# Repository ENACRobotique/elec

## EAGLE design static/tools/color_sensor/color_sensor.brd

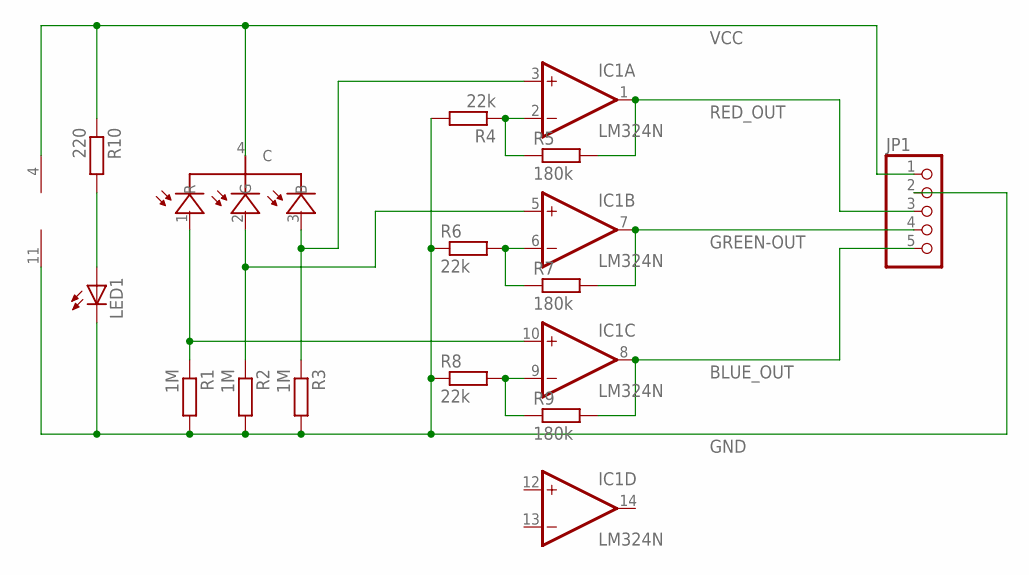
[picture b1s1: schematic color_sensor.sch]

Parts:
IC1: LM324N; DIL14
JP1: PINHD-1X5; 1X05
LED1: LED5MM
R1, R2, R3: 1M; 0207/10
R4, R6, R8: 22k; 0207/10
R5, R7, R9: 180k; 0207/10
R10: 220; 0207/10
U$1: KPS-5130PD7C

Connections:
BLUE_OUT: IC1.8 (OUT), JP1.5, R9.2
GND: IC1.11 (V-), JP1.2, LED1.K (C), R1.2, R2.2, R3.2, R4.2, R6.1, R8.1
GREEN-OUT: IC1.7 (OUT), JP1.4, R7.2
unnamed: IC1.10 (+IN), R1.1, U$1.1 (R)
unnamed: IC1.5 (+IN), R2.1, U$1.2 (G)
unnamed: IC1.3 (+IN), R3.1, U$1.3 (B)
unnamed: LED1.A, R10.2
unnamed: IC1.2 (-IN), R4.1, R5.1
unnamed: IC1.6 (-IN), R6.2, R7.1
unnamed: IC1.9 (-IN), R8.2, R9.1
RED_OUT: IC1.1 (OUT), JP1.3, R5.2
VCC: IC1.4 (V+), JP1.1, R10.1, U$1.4 (C)

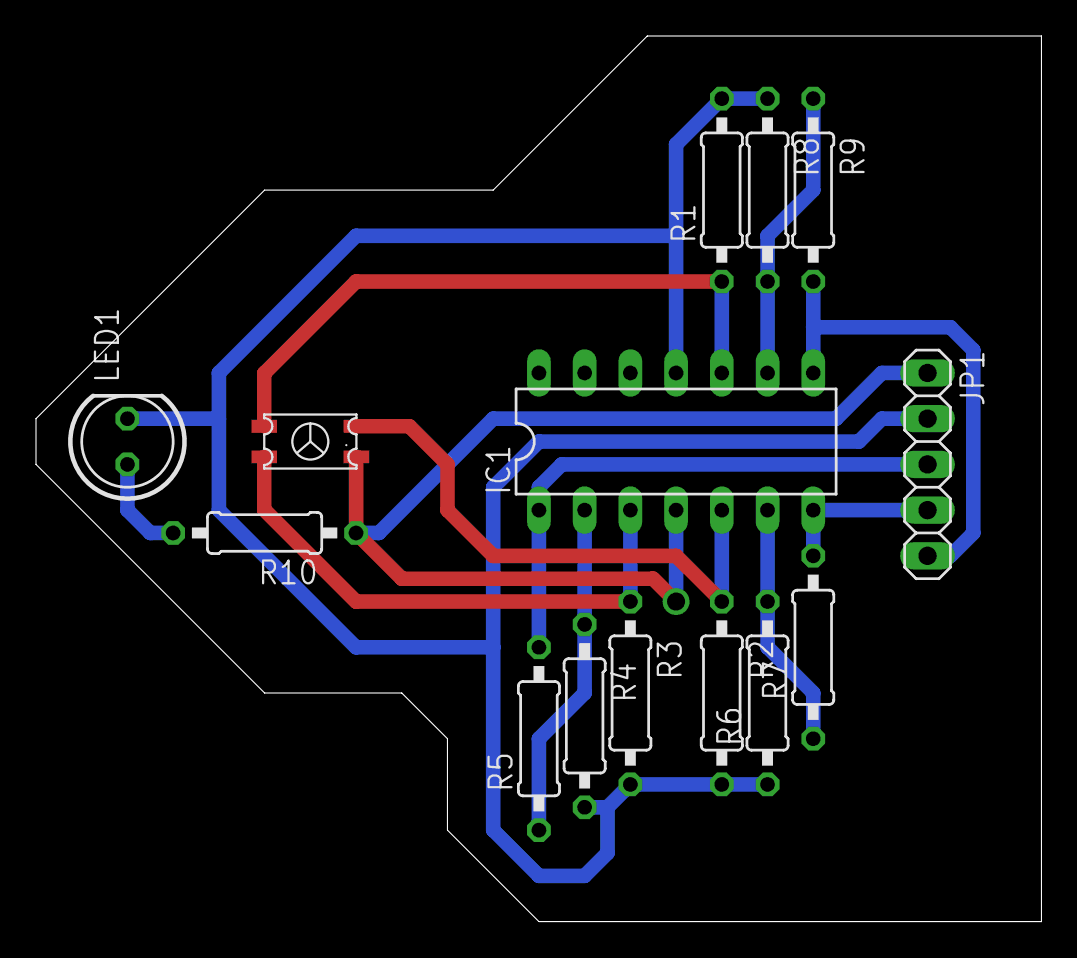
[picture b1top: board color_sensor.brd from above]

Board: 2 copper layers, 55.9 x 49.2 mm, 14 parts (0 on the bottom side), 12 nets.

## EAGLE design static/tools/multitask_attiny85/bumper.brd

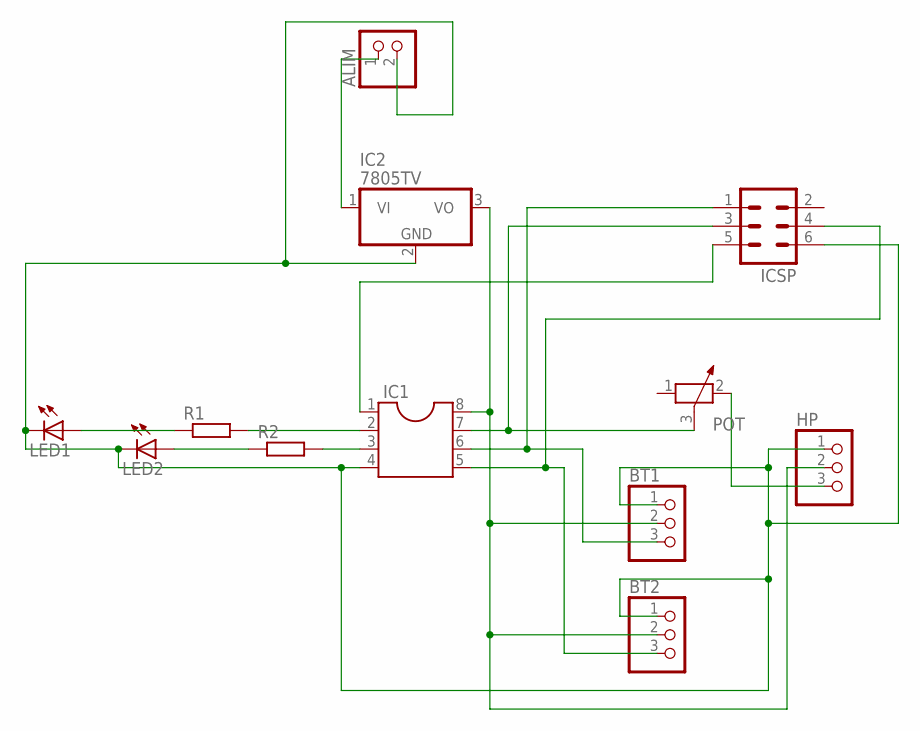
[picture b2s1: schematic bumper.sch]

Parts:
ALIM: PINHD-1X2; 1X02
BT1, BT2: PINHD-1X3; 1X03
HP: PINHD-1X3; 1X03
IC1: DIL8S; SOCKET-08
IC2: 7805TV; TO220V
ICSP: ML6
LED1, LED2: LED5MM
POT: POTENTIOMETER_PT-10; PT-10
R1, R2: R-EU_0204/7; 0204/7

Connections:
unnamed: LED1.A, R1.1
unnamed: LED2.A, R2.1
unnamed: IC1.3, R2.2
unnamed: IC1.2, R1.2
unnamed: BT1.2, BT2.2, HP.2, IC1.8, IC2.3 (VO)
unnamed: ALIM.2, BT1.1, BT2.1, HP.1, IC1.4, IC2.2 (GND), ICSP.6, LED1.K (C), LED2.K (C)
unnamed: IC1.7, ICSP.3, POT.3
unnamed: BT1.3, IC1.6, ICSP.1
unnamed: BT2.3, IC1.5, ICSP.4
unnamed: HP.3, POT.2
unnamed: IC1.1, ICSP.5
unnamed: ALIM.1, IC2.1 (VI)

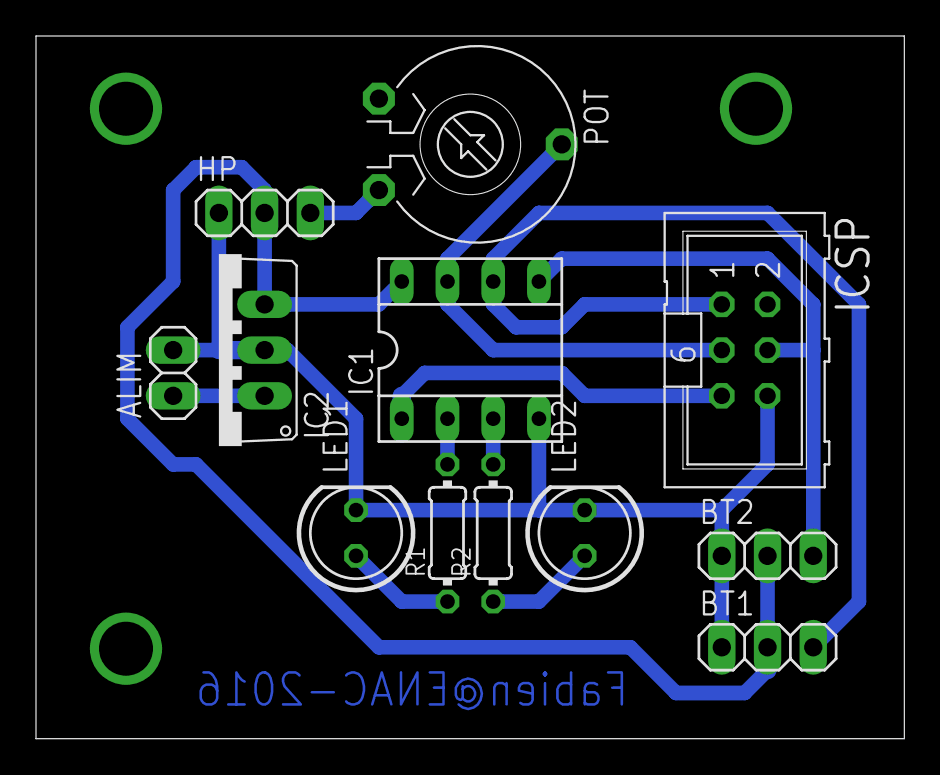
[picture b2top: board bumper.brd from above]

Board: 2 copper layers, 48.2 x 39.0 mm, 12 parts (0 on the bottom side), 12 nets.

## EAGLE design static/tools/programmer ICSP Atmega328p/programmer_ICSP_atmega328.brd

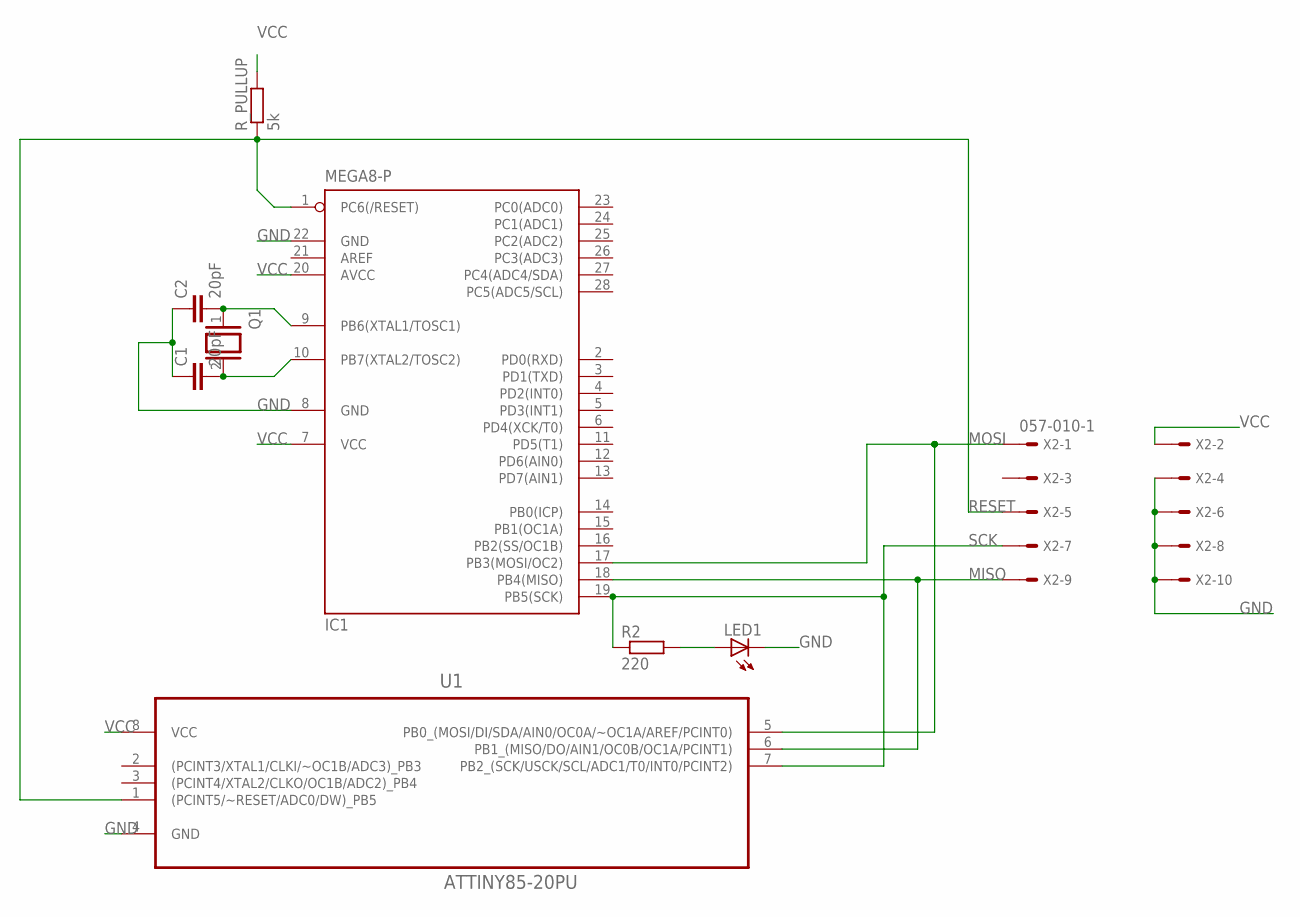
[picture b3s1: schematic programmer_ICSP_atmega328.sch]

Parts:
C1, C2: 20pF; C5B5
IC1: MEGA8-P; DIL28-3
LED1: LED3MM
Q1: XTAL/S; QS
R2: 220; 0207/7
R_PULLUP: 5k; 0207/7
U1: ATTINY85-20PU; DIP254P762X533-8
X2: 057-010-1

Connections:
GND: C1.1, C2.1, IC1.8 (GND), IC1.22 (GND), LED1.K (C), U1.4 (GND), X2.4, X2.6, X2.8, X2.10
JUJU: LED1.A, R2.2
MISO: IC1.18 (PB4(MISO)), U1.6 (PB1_(MISO/DO/AIN1/OC0B/OC1A/PCINT1)), X2.9
MOSI: IC1.17 (PB3(MOSI/OC2)), U1.5 (PB0_(MOSI/DI/SDA/AIN0/OC0A/~OC1A/AREF/P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), X2.1
unnamed: C2.2, IC1.9 (PB6(XTAL1/TOSC1)), Q1.1
unnamed: C1.2, IC1.10 (PB7(XTAL2/TOSC2)), Q1.2
RESET: IC1.1 (PC6(/RESET)), R_PULLUP.1, U1.1 ((PCINT5/~RESET/ADC0/DW)_PB5), X2.5
SCK: IC1.19 (PB5(SCK)), R2.1, U1.7 (PB2_(SCK/USCK/SCL/ADC1/T0/INT0/PCINT2)), X2.7
VCC: IC1.7 (VCC), IC1.20 (AVCC), R_PULLUP.2, U1.8 (VCC), X2.2

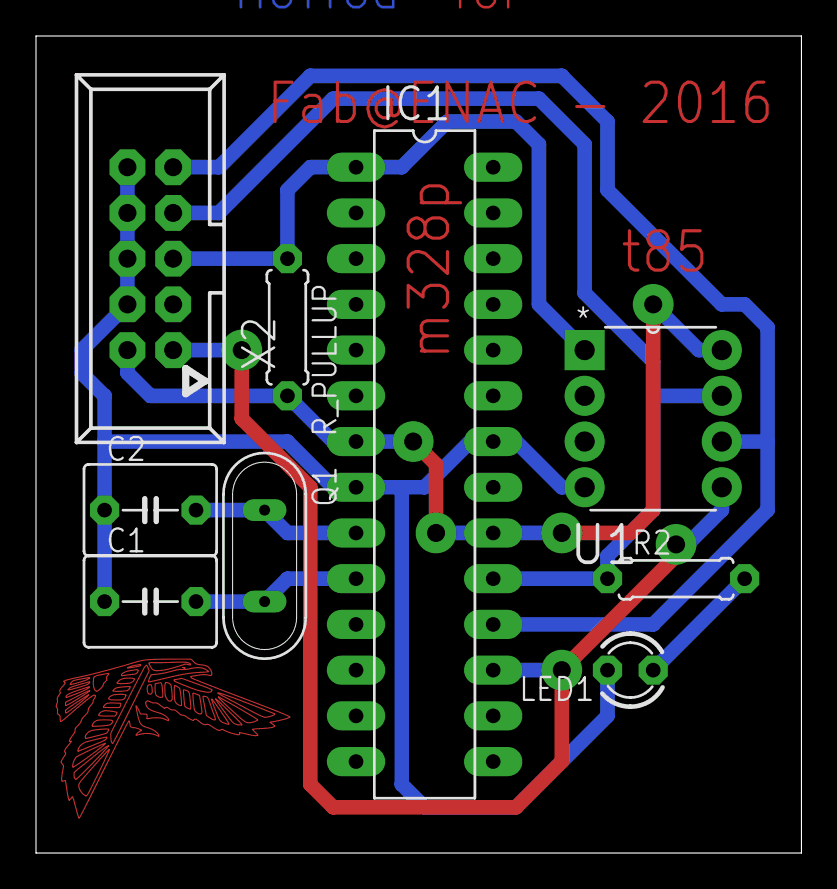
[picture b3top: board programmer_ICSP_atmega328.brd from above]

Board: 2 copper layers, 42.5 x 45.4 mm, 9 parts (0 on the bottom side), 9 nets.

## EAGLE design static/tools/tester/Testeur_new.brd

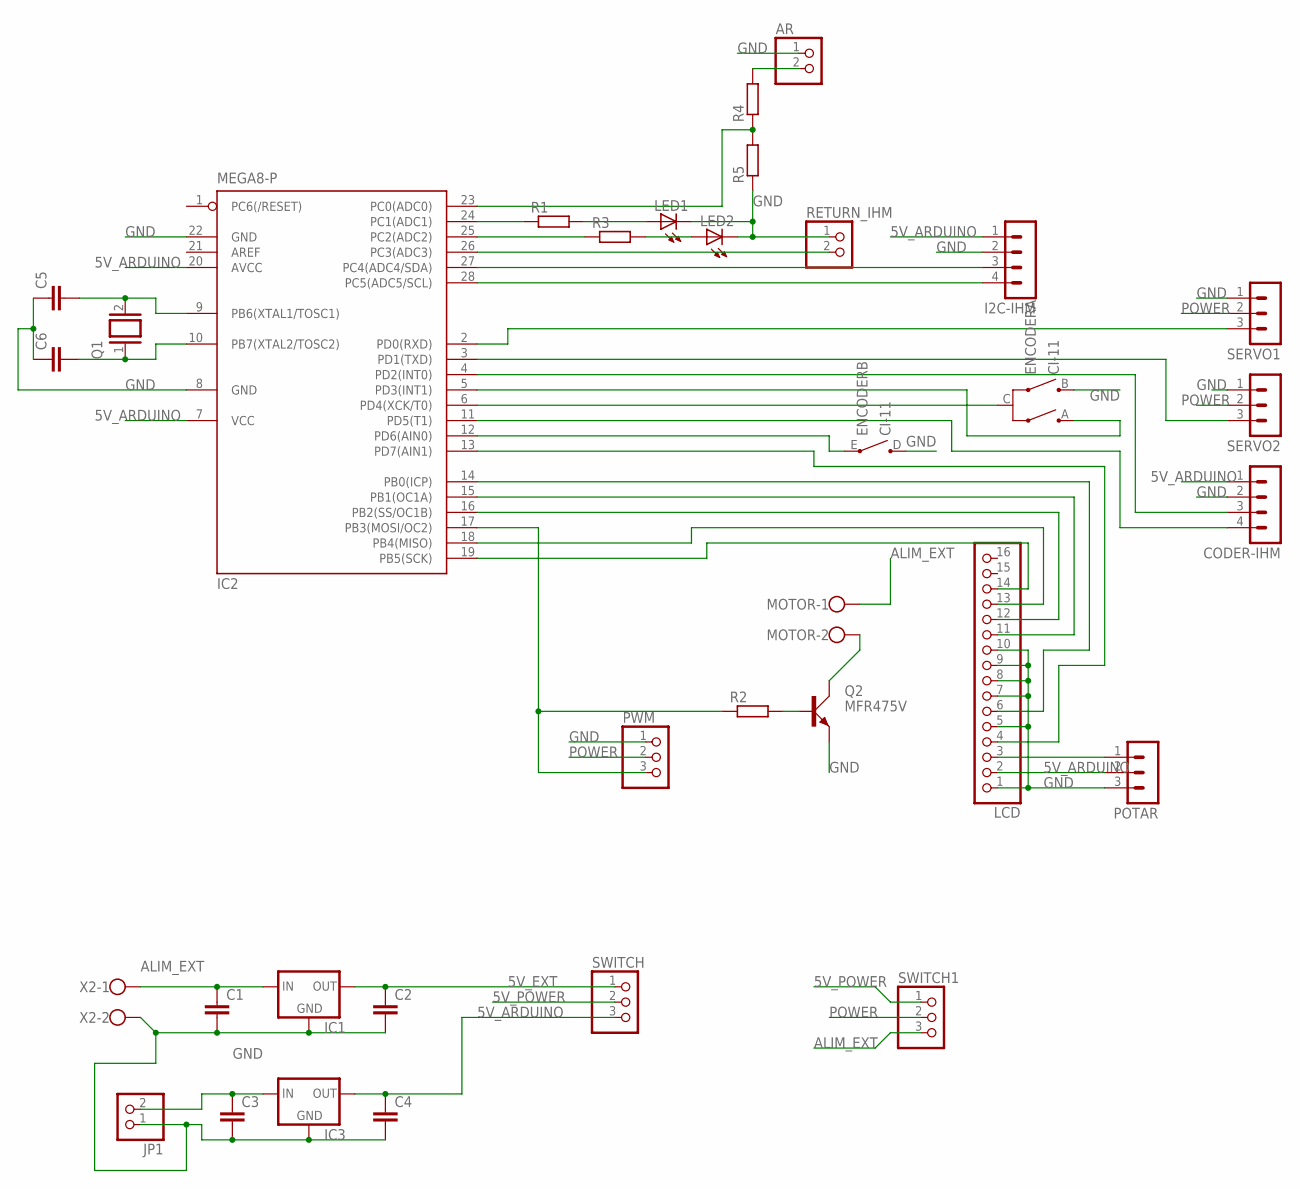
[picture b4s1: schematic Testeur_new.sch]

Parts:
AR: PINHD-1X2; 1X02
C1, C2, C3, C4: C5/3.5; C5B3.5
C5, C6: C5/5; C5B5
CODER-IHM: MA04-1
ENCODER: CI-11
I2C-IHM: MA04-1
IC1, IC3: 78XXS
IC2: MEGA8-P; DIL28-3
JP1: PINHD-1X2; 1X02
LCD: PINHD-1X16; 1X16
LED1, LED2: LED5MM
MOTOR: W237-102
POTAR: MA03-1
PWM: PINHD-1X3; 1X03
Q1: XTAL/S; QS
Q2: MFR475V; TO220AV
R1, R2, R3, R4, R5: R-EU_0204/7; 0204/7
RETURN_IHM: PINHD-1X2; 1X02
SERVO1, SERVO2: MA03-1
SWITCH, SWITCH1: PINHD-1X3; 1X03
X2: W237-102

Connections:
5V_ARDUINO: C4.1, CODER-IHM.1, I2C-IHM.1, IC2.7 (VCC), IC2.20 (AVCC), IC3.OUT, LCD.2, POTAR.2, SWITCH.3
5V_EXT: C2.1, IC1.OUT, SWITCH.1
5V_POWER: SWITCH.2, SWITCH1.1
ALIM_EXT: C1.1, IC1.IN, MOTOR.1, SWITCH1.3, X2.1
GND: AR.1, C1.2, C2.2, C3.2, C4.2, C5.1, C6.1, CODER-IHM.2, ENCODER.B, ENCODER.D, I2C-IHM.2, IC1.GND, IC2.8 (GND), IC2.22 (GND), IC3.GND, JP1.1, LCD.1, LCD.5, LCD.7, LCD.8, LCD.9, LCD.10, LED1.K (C), LED2.K (C), POTAR.3, PWM.1, Q2.E, R5.1, RETURN_IHM.1, SERVO1.1, SERVO2.1, X2.2
unnamed: IC2.26 (PC3(ADC3)), RETURN_IHM.2
unnamed: IC2.15 (PB1(OC1A)), LCD.11
unnamed: IC2.16 (PB2(SS/OC1B)), LCD.12
unnamed: IC2.18 (PB4(MISO)), LCD.13
unnamed: ENCODER.C, IC2.6 (PD4(XCK/T0))
unnamed: IC2.19 (PB5(SCK)), LCD.14
unnamed: Q2.B, R2.2
unnamed: LED2.A, R3.2
unnamed: I2C-IHM.3, IC2.27 (PC4(ADC4/SDA))
unnamed: I2C-IHM.4, IC2.28 (PC5(ADC5/SCL))
unnamed: LED1.A, R1.2
unnamed: ENCODER.E, IC2.12 (PD6(AIN0))
unnamed: IC2.2 (PD0(RXD)), SERVO1.3
unnamed: C3.1, IC3.IN, JP1.2
unnamed: CODER-IHM.3, IC2.4 (PD2(INT0))
unnamed: CODER-IHM.4, IC2.11 (PD5(T1))
unnamed: ENCODER.A, IC2.5 (PD3(INT1))
unnamed: IC2.24 (PC1(ADC1)), R1.1
unnamed: IC2.25 (PC2(ADC2)), R3.1
unnamed: AR.2, R4.2
unnamed: IC2.13 (PD7(AIN1)), LCD.4
unnamed: IC2.14 (PB0(ICP)), LCD.6
unnamed: C6.2, IC2.10 (PB7(XTAL2/TOSC2)), Q1.1
unnamed: C5.2, IC2.9 (PB6(XTAL1/TOSC1)), Q1.2
unnamed: IC2.17 (PB3(MOSI/OC2)), PWM.3, R2.1
unnamed: R4.1, R5.2
unnamed: LCD.3, POTAR.1
unnamed: MOTOR.2, Q2.C
unnamed: IC2.3 (PD1(TXD)), SERVO2.3
POWER: PWM.2, SERVO1.2, SERVO2.2, SWITCH1.2

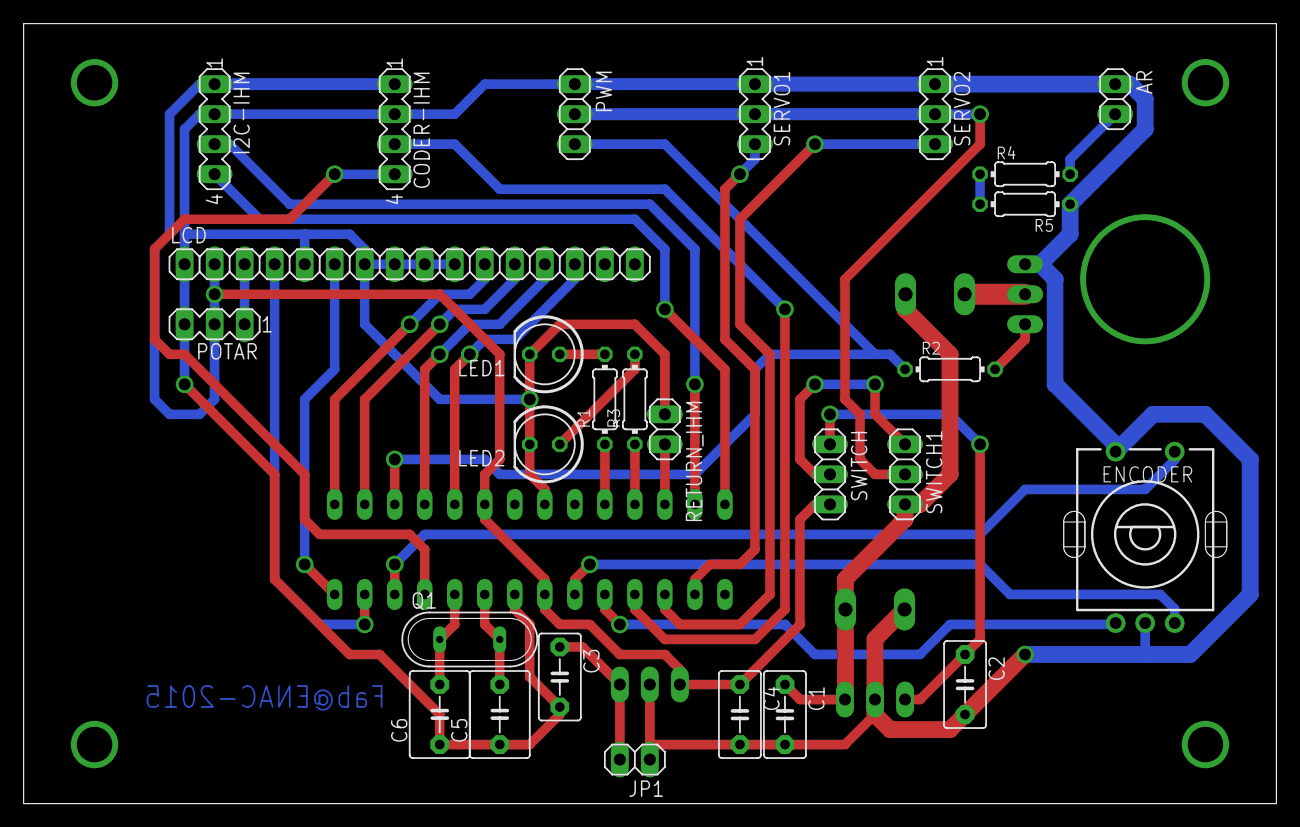
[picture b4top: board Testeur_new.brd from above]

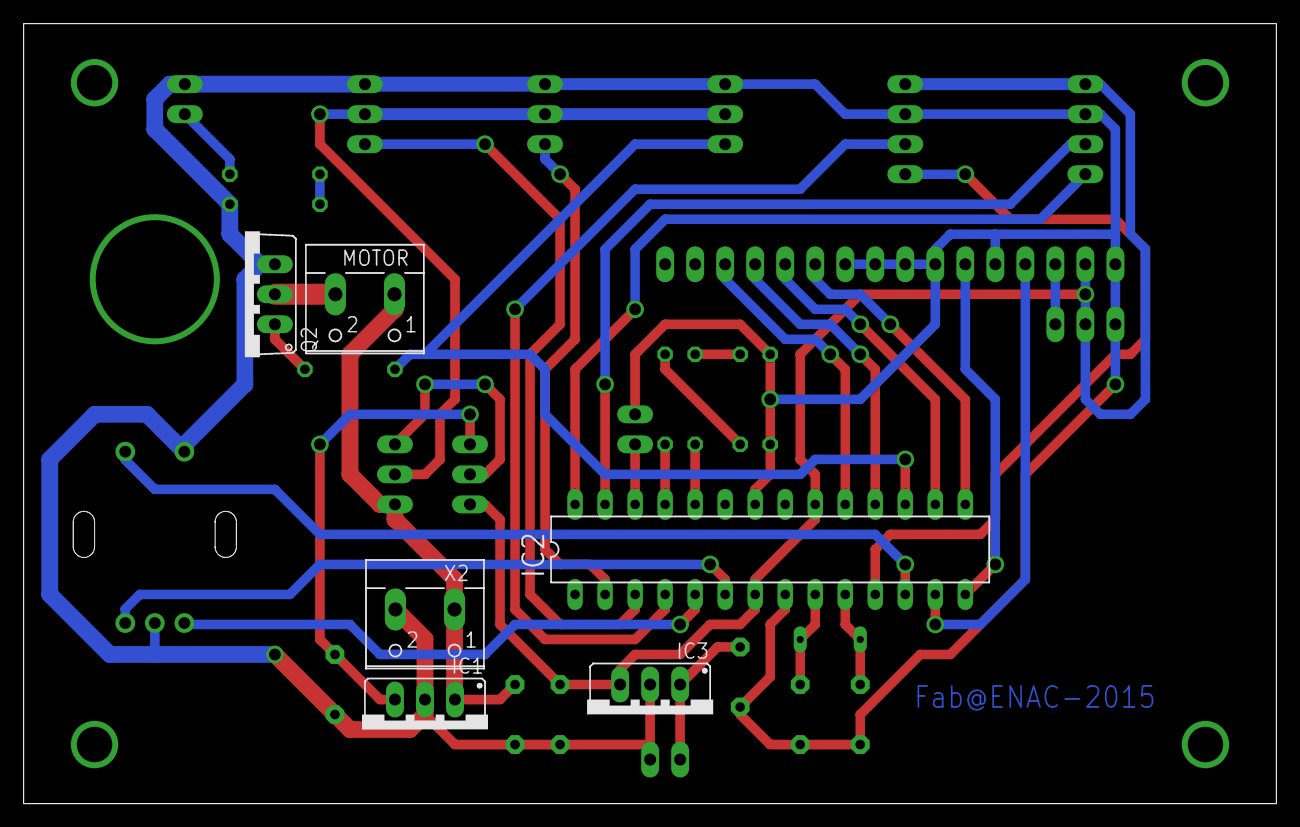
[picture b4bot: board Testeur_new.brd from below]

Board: 2 copper layers, 106.0 x 66.0 mm, 33 parts (6 on the bottom side), 35 nets.

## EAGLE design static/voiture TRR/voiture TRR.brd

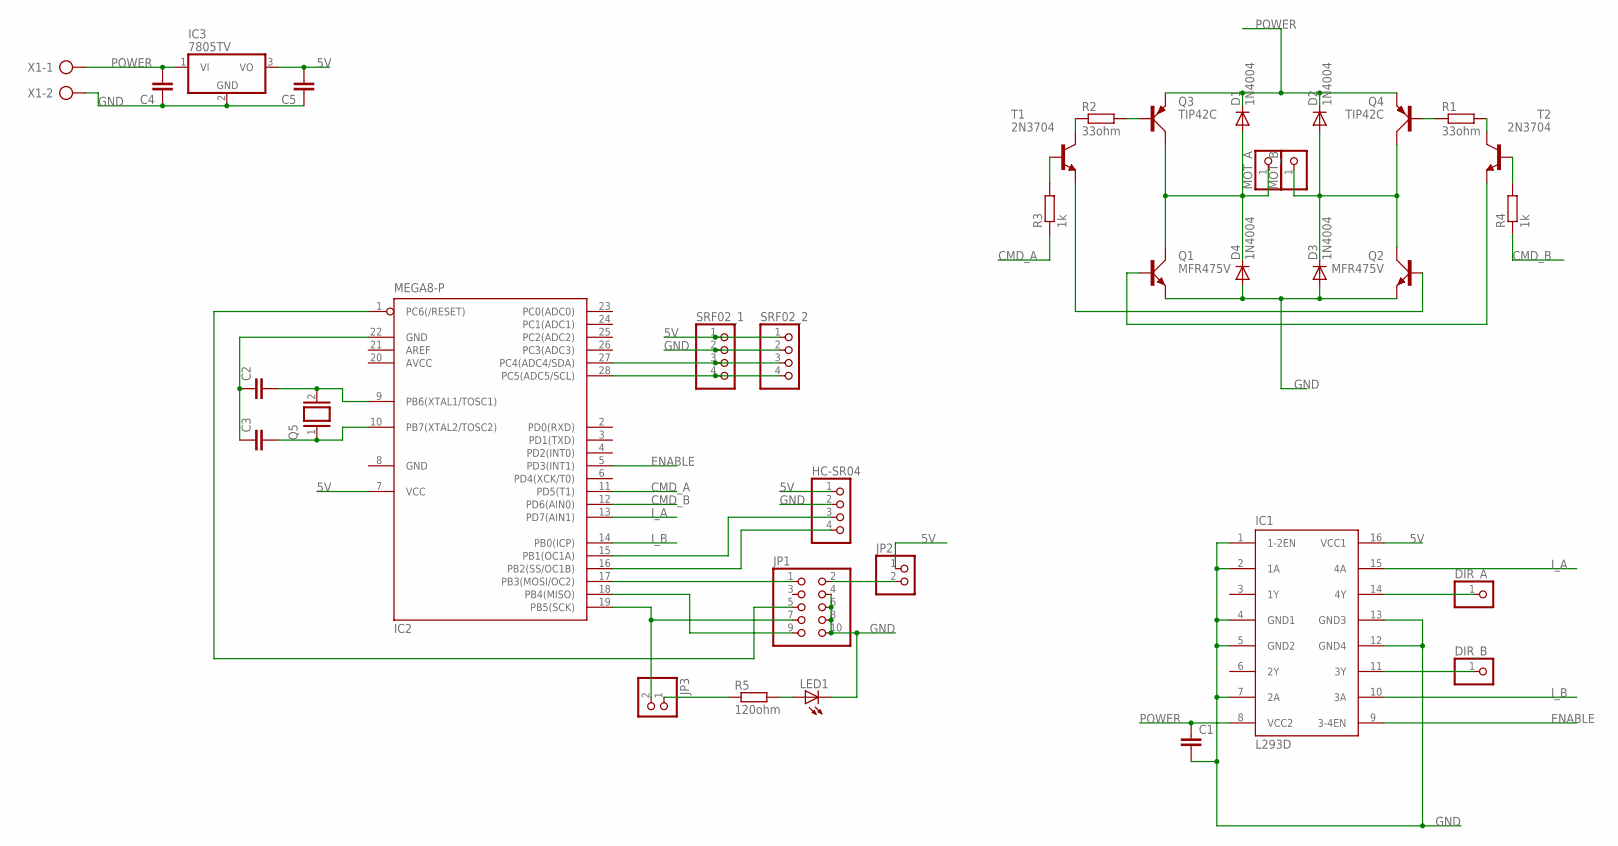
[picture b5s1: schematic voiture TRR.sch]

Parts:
C1: C-EU025-050X050; C025-050X050
C2, C3, C4, C5: C5/2.5; C5B2.5
D1, D2, D3, D4: 1N4004; DO41-10
DIR_A: PINHD-1X1; 1X01
DIR_B: PINHD-1X1; 1X01
HC-SR04: PINHD-1X4; 1X04
IC1: L293D; DIL16
IC2: MEGA8-P; DIL28-3
IC3: 7805TV; TO220V
JP1: PINHD-2X5; 2X05
JP2, JP3: PINHD-1X2; 1X02
LED1: LED5MM
MOT_A: PINHD-1X1; 1X01
MOT_B: PINHD-1X1; 1X01
Q1, Q2: MFR475V; TO220AV
Q3, Q4: TIP42C; TO220AV
Q5: XTAL/S; QS
R1, R2: 33ohm; 0204/7
R3, R4: 1k; 0204/7
R5: 120ohm; 0204/7
SRF02_1, SRF02_2: PINHD-1X4; 1X04
T1, T2: 2N3704; TO92
X1: AK300/2

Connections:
5V: C5.2, HC-SR04.1, IC1.16 (VCC1), IC2.7 (VCC), IC2.20 (AVCC), IC3.3 (VO), JP2.1, SRF02_1.1, SRF02_2.1
CMD_A: IC2.11 (PD5(T1)), R3.1
CMD_B: IC2.12 (PD6(AIN0)), R4.1
ENABLE: IC1.9 (3-4EN), IC2.5 (PD3(INT1))
GND: C1.2, C2.1, C3.1, C4.1, C5.1, D3.A, D4.A, HC-SR04.2, IC1.1 (1-2EN), IC1.2 (1A), IC1.4 (GND1), IC1.5 (GND2), IC1.7 (2A), IC1.12 (GND4), IC1.13 (GND3), IC2.8 (GND), IC2.22 (GND), IC3.2 (GND), JP1.4, JP1.6, JP1.8, JP1.10, LED1.K (C), Q1.E, Q2.E, SRF02_1.2, SRF02_2.2, X1.2
I_A: IC1.15 (4A), IC2.13 (PD7(AIN1))
I_B: IC1.10 (3A), IC2.14 (PB0(ICP))
unnamed: D1.A, D4.C, MOT_A.1, Q1.C, Q3.C
unnamed: Q3.B, R2.2
unnamed: DIR_A.1, IC1.14 (4Y)
unnamed: DIR_B.1, IC1.11 (3Y)
unnamed: R2.1, T1.2 (C)
unnamed: D2.A, D3.C, MOT_B.1, Q2.C, Q4.C
unnamed: Q2.B, T1.3 (E)
unnamed: Q4.B, R1.1
unnamed: R1.2, T2.2 (C)
unnamed: Q1.B, T2.3 (E)
unnamed: R4.2, T2.1 (B)
unnamed: R3.2, T1.1 (B)
unnamed: C3.2, IC2.10 (PB7(XTAL2/TOSC2)), Q5.1
unnamed: C2.2, IC2.9 (PB6(XTAL1/TOSC1)), Q5.2
unnamed: IC2.17 (PB3(MOSI/OC2)), JP1.1
unnamed: IC2.1 (PC6(/RESET)), JP1.5
unnamed: IC2.19 (PB5(SCK)), JP1.7, JP3.2
unnamed: IC2.18 (PB4(MISO)), JP1.9
unnamed: JP3.1, R5.1
unnamed: JP1.2, JP2.2
unnamed: LED1.A, R5.2
unnamed: IC2.27 (PC4(ADC4/SDA)), SRF02_1.3, SRF02_2.3
unnamed: IC2.28 (PC5(ADC5/SCL)), SRF02_1.4, SRF02_2.4
unnamed: HC-SR04.3, IC2.15 (PB1(OC1A))
unnamed: HC-SR04.4, IC2.16 (PB2(SS/OC1B))
POWER: C1.1, C4.2, D1.C, D2.C, IC1.8 (VCC2), IC3.1 (VI), Q3.E, Q4.E, X1.1

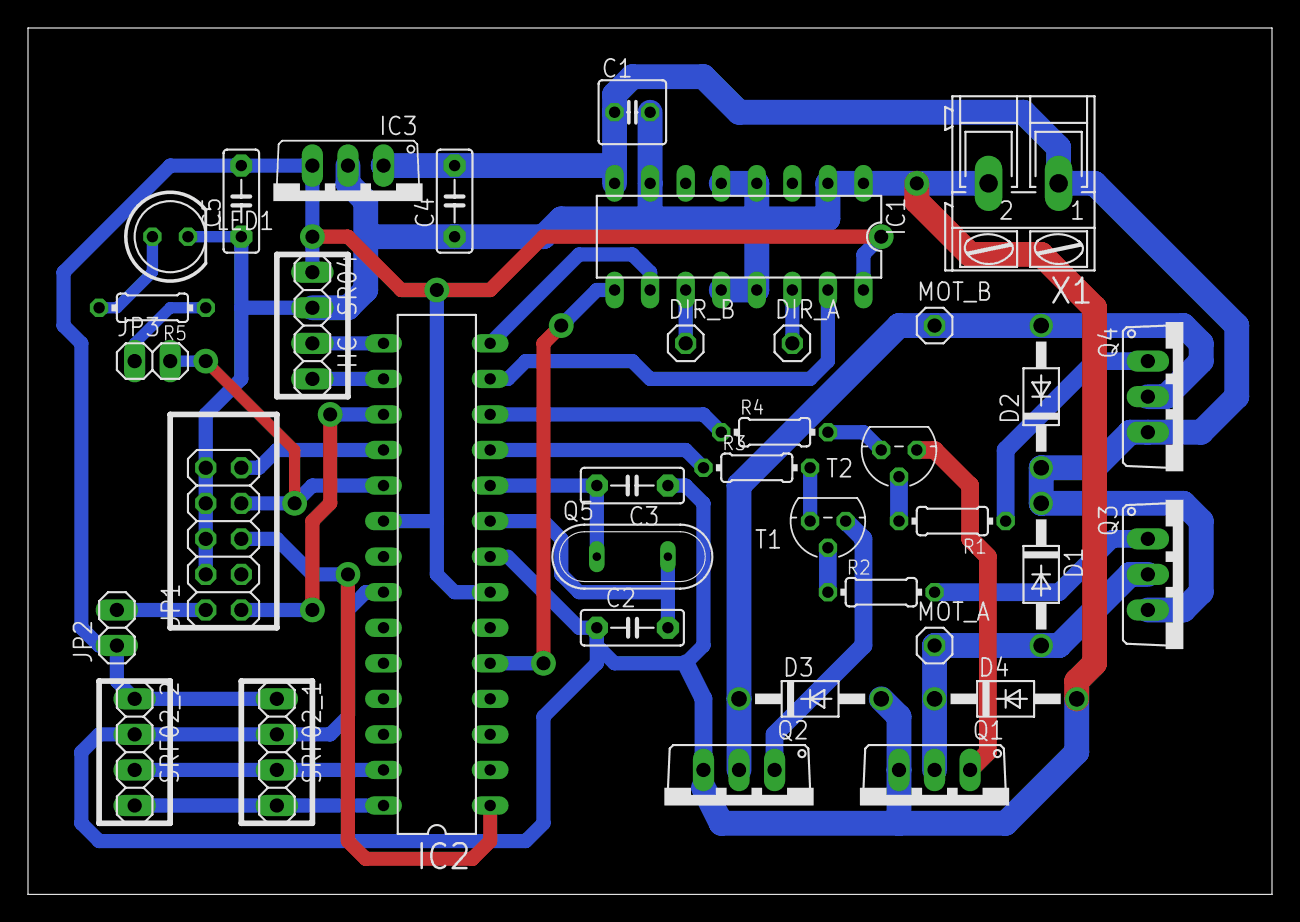
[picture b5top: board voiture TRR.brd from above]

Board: 2 copper layers, 88.9 x 61.9 mm, 36 parts (0 on the bottom side), 33 nets.
